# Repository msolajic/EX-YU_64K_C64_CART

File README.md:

# EX-YU_64K_C64_CART
64k Bankswitching Cartridge for the Commodore 64

See more here:
https://blog.8bitchip.info/168-dissecting-ex-yugoslavian-c64-cartridges-part-3/

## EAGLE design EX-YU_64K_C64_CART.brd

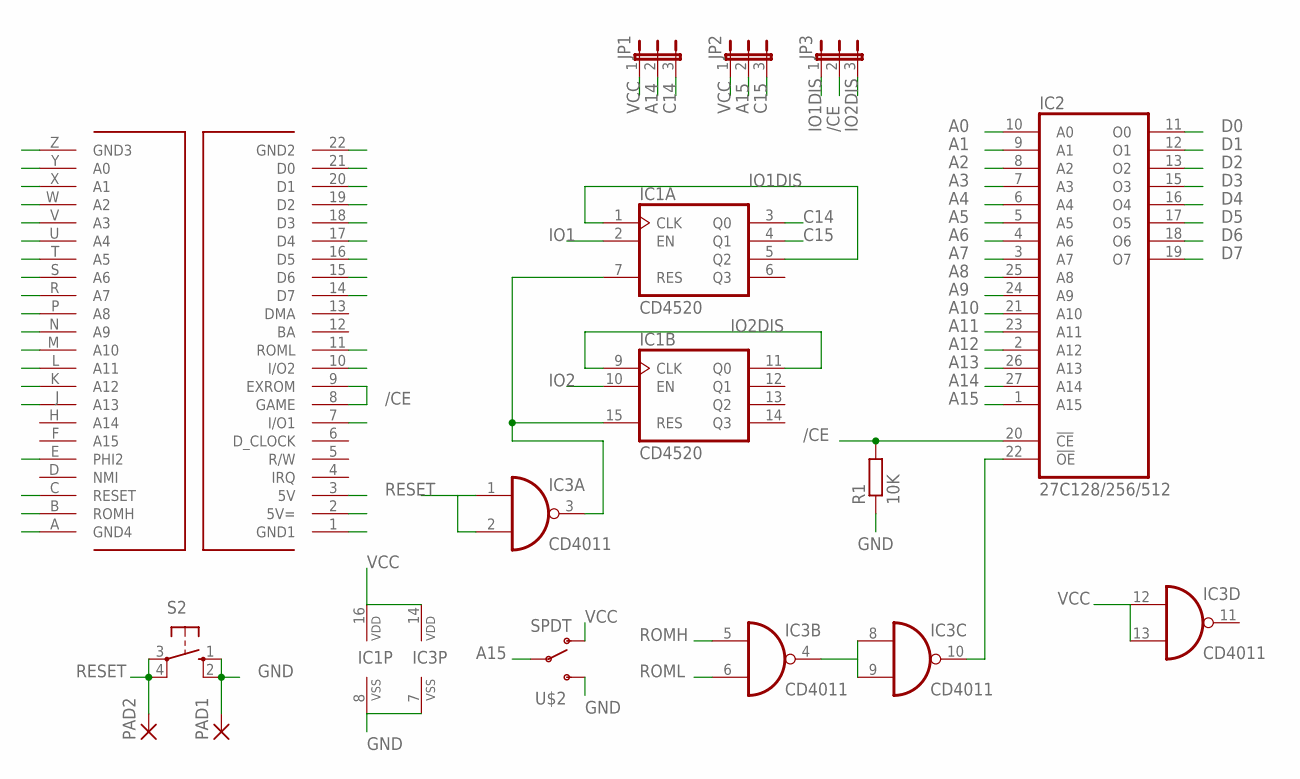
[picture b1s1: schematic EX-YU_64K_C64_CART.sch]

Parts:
IC1: CD4520; DIL16
IC2: 27C128/256/512; DIL28
IC3: CD4011; DIL14
JP1, JP2, JP3: JP2E; JP2
PAD1, PAD2: SMD5; SMD2,54-5,08
R1: 10K; 0207/10
S2: 10-XX; B3F-10XX
U$1: C64_EXPANSION__CARTRIDGE
U$2: SPDT; SPDT-SLIDE

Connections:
/CE: IC2.20 (!CE), JP3.2, R1.2, U$1.8 (GAME), U$1.9 (EXROM)
A0: IC2.10 (A0), U$1.Y (A0)
A1: IC2.9 (A1), U$1.X (A1)
A2: IC2.8 (A2), U$1.W (A2)
A3: IC2.7 (A3), U$1.V (A3)
A4: IC2.6 (A4), U$1.U (A4)
A5: IC2.5 (A5), U$1.T (A5)
A6: IC2.4 (A6), U$1.S (A6)
A7: IC2.3 (A7), U$1.R (A7)
A8: IC2.25 (A8), U$1.P (A8)
A9: IC2.24 (A9), U$1.N (A9)
A10: IC2.21 (A10), U$1.M (A10)
A11: IC2.23 (A11), U$1.L (A11)
A12: IC2.2 (A12), U$1.K (A12)
A13: IC2.26 (A13), U$1.J (A13)
A14: IC2.27 (A14), JP1.2
A15: IC2.1 (A15), JP2.2, U$2.2
C14: IC1.3 (Q0), JP1.3
C15: IC1.4 (Q1), JP2.3
D0: IC2.11 (O0), U$1.21 (D0)
D1: IC2.12 (O1), U$1.20 (D1)
D2: IC2.13 (O2), U$1.19 (D2)
D3: IC2.15 (O3), U$1.18 (D3)
D4: IC2.16 (O4), U$1.17 (D4)
D5: IC2.17 (O5), U$1.16 (D5)
D6: IC2.18 (O6), U$1.15 (D6)
D7: IC2.19 (O7), U$1.14 (D7)
GND: IC1.8 (VSS), IC2.14 (GND), IC3.7 (VSS), PAD1.1, R1.1, S2.1 (S), S2.2 (S1), U$1.1 (GND1), U$1.22 (GND2), U$1.A (GND4), U$1.Z (GND3), U$2.3
IO1: IC1.2 (EN), U$1.7 (I/O1)
IO1DIS: IC1.1 (CLK), IC1.5 (Q2), JP3.1
IO2: IC1.10 (EN), U$1.10 (I/O2)
IO2DIS: IC1.9 (CLK), IC1.11 (Q0), JP3.3
unnamed: IC1.7 (RES), IC1.15 (RES), IC3.3 (O)
unnamed: IC3.4 (O), IC3.8 (I0), IC3.9 (I1)
unnamed: IC2.22 (!OE), IC3.10 (O)
PHI2: U$1.E (PHI2)
RESET: IC3.1 (I0), IC3.2 (I1), PAD2.1, S2.3, S2.4 (P1), U$1.C (RESET)
ROMH: IC3.5 (I0), U$1.B (ROMH)
ROML: IC3.6 (I1), U$1.11 (ROML)
VCC: IC1.16 (VDD), IC2.28 (VCC), IC3.12 (I0), IC3.13 (I1), IC3.14 (VDD), JP1.1, JP2.1, U$1.2 (5V=), U$1.3 (5V), U$2.1

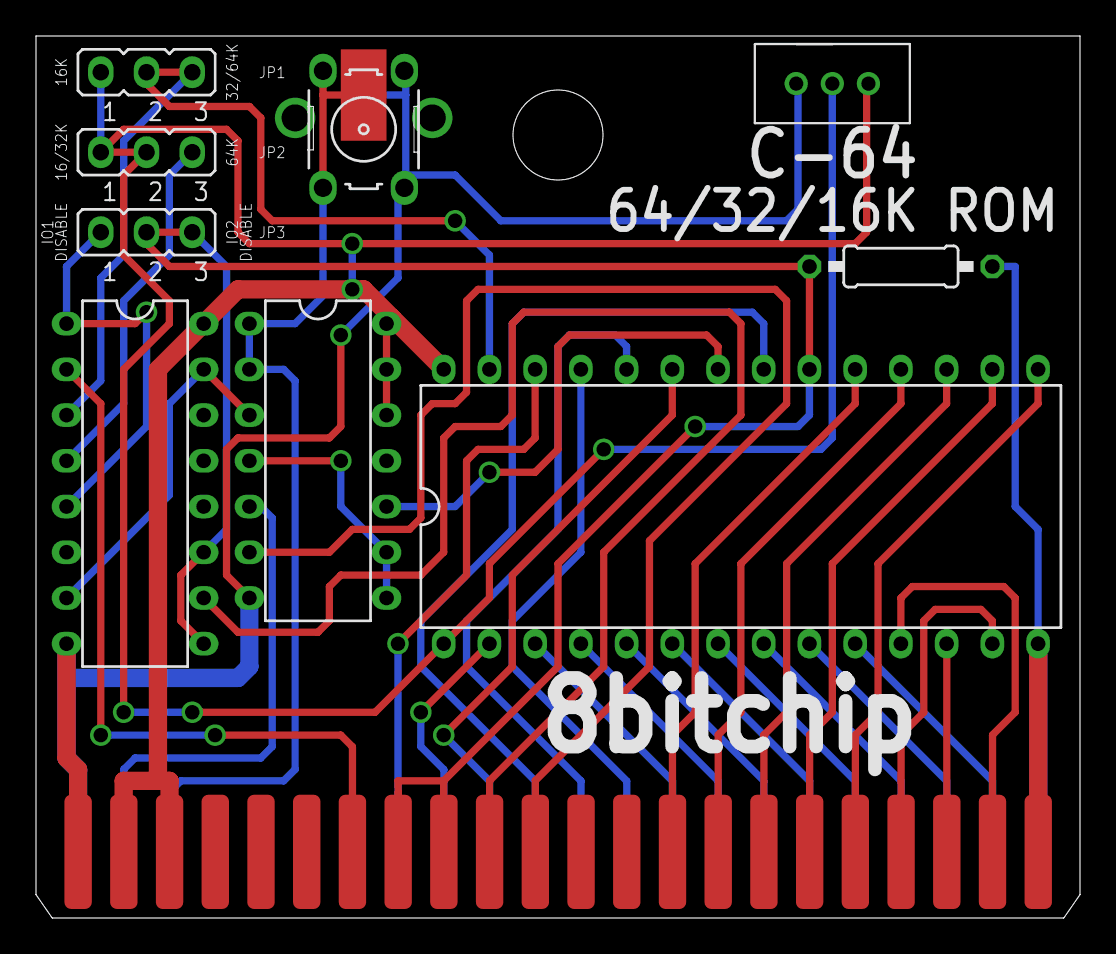
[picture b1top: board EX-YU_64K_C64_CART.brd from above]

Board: 2 copper layers, 58.0 x 49.0 mm, 12 parts (1 on the bottom side), 39 nets.
